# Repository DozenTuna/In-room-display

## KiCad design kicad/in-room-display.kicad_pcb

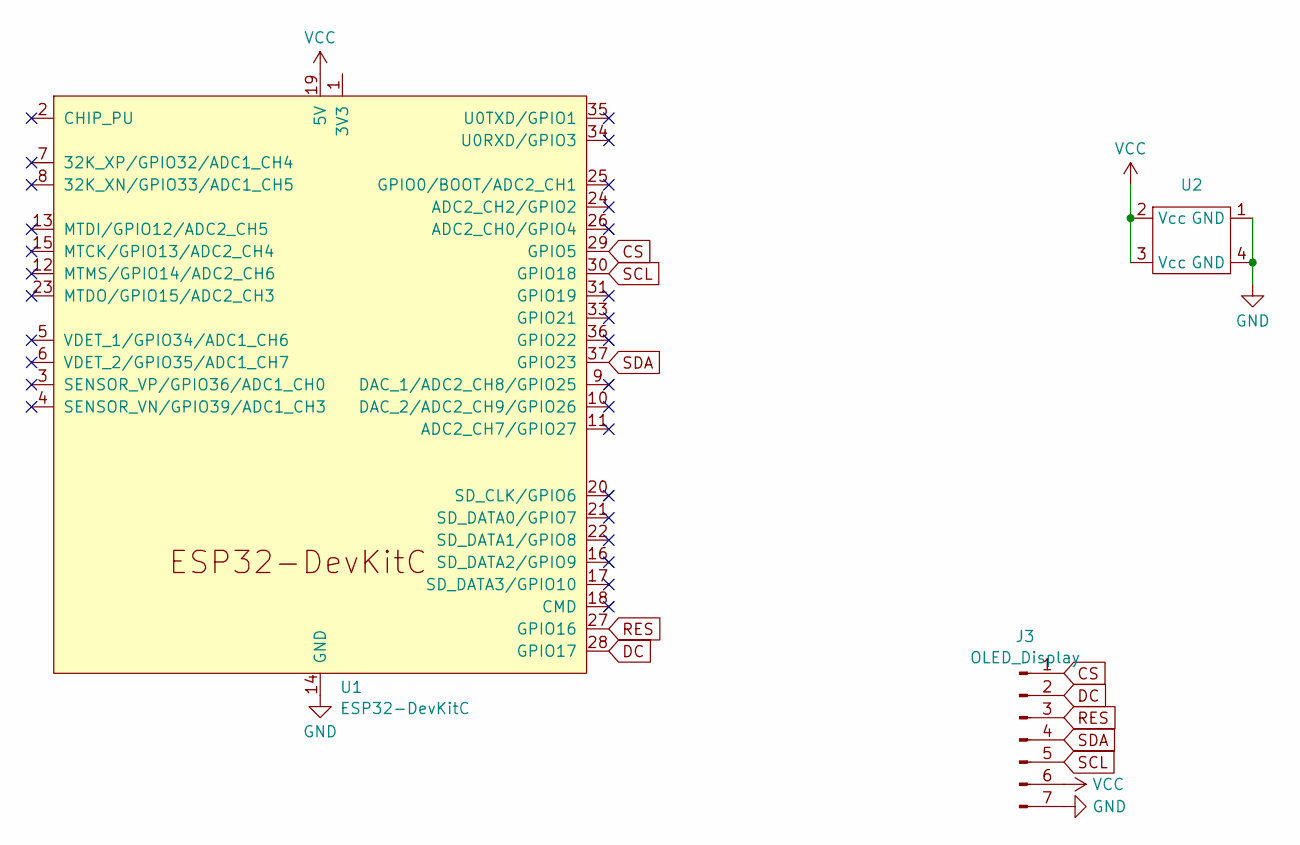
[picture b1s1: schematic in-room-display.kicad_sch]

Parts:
J3: OLED_Display; PinHeader_1x07_P2.54mm_Vertical
U1: ESP32-DevKitC
U2: DIP-4_300_ELL

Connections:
CS: J3.1, U1.29 (GPIO5)
DC: J3.2, U1.28 (GPIO17)
GND: J3.7, U1.14 (GND), U1.32 (GND), U1.38 (GND), U2.1 (GND), U2.4 (GND)
RES: J3.3, U1.27 (GPIO16)
SCL: J3.5, U1.30 (GPIO18)
SDA: J3.4, U1.37 (GPIO23)
VCC: J3.6, U1.19 (5V), U2.2 (Vcc), U2.3 (Vcc)

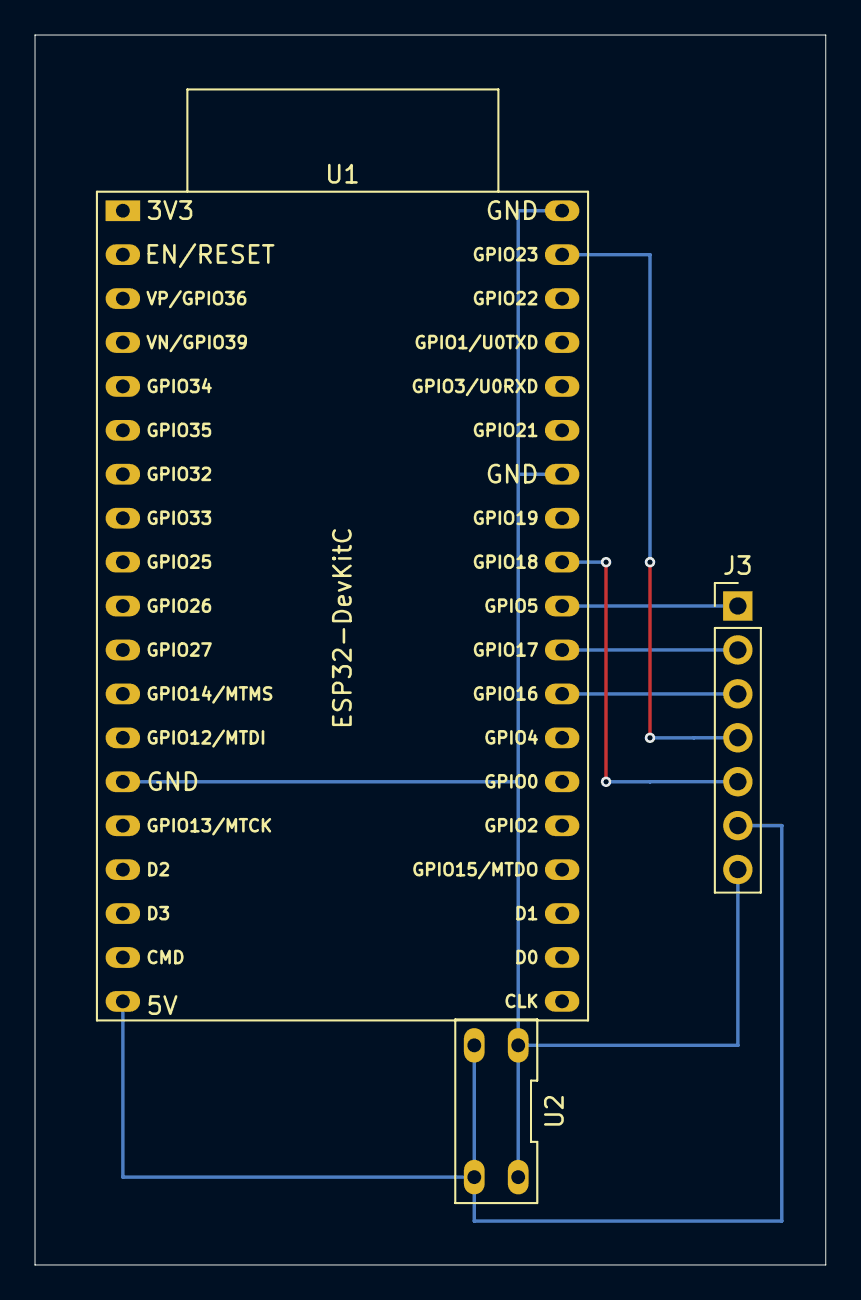
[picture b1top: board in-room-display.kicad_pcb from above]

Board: 2 copper layers, 45.7 x 71.1 mm, 3 parts (0 on the bottom side), 7 nets.

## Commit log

2024-06-21 SSD1331への画像表示に成功
2024-06-26 update: delete random and add error display
2024-06-26 create kicad project
2024-06-26 create pcb layout
2024-06-26 create schematic for ST7789
2024-06-27 ひとまず形になった
2024-07-03 add: server-side codes
2024-11-28 backup
